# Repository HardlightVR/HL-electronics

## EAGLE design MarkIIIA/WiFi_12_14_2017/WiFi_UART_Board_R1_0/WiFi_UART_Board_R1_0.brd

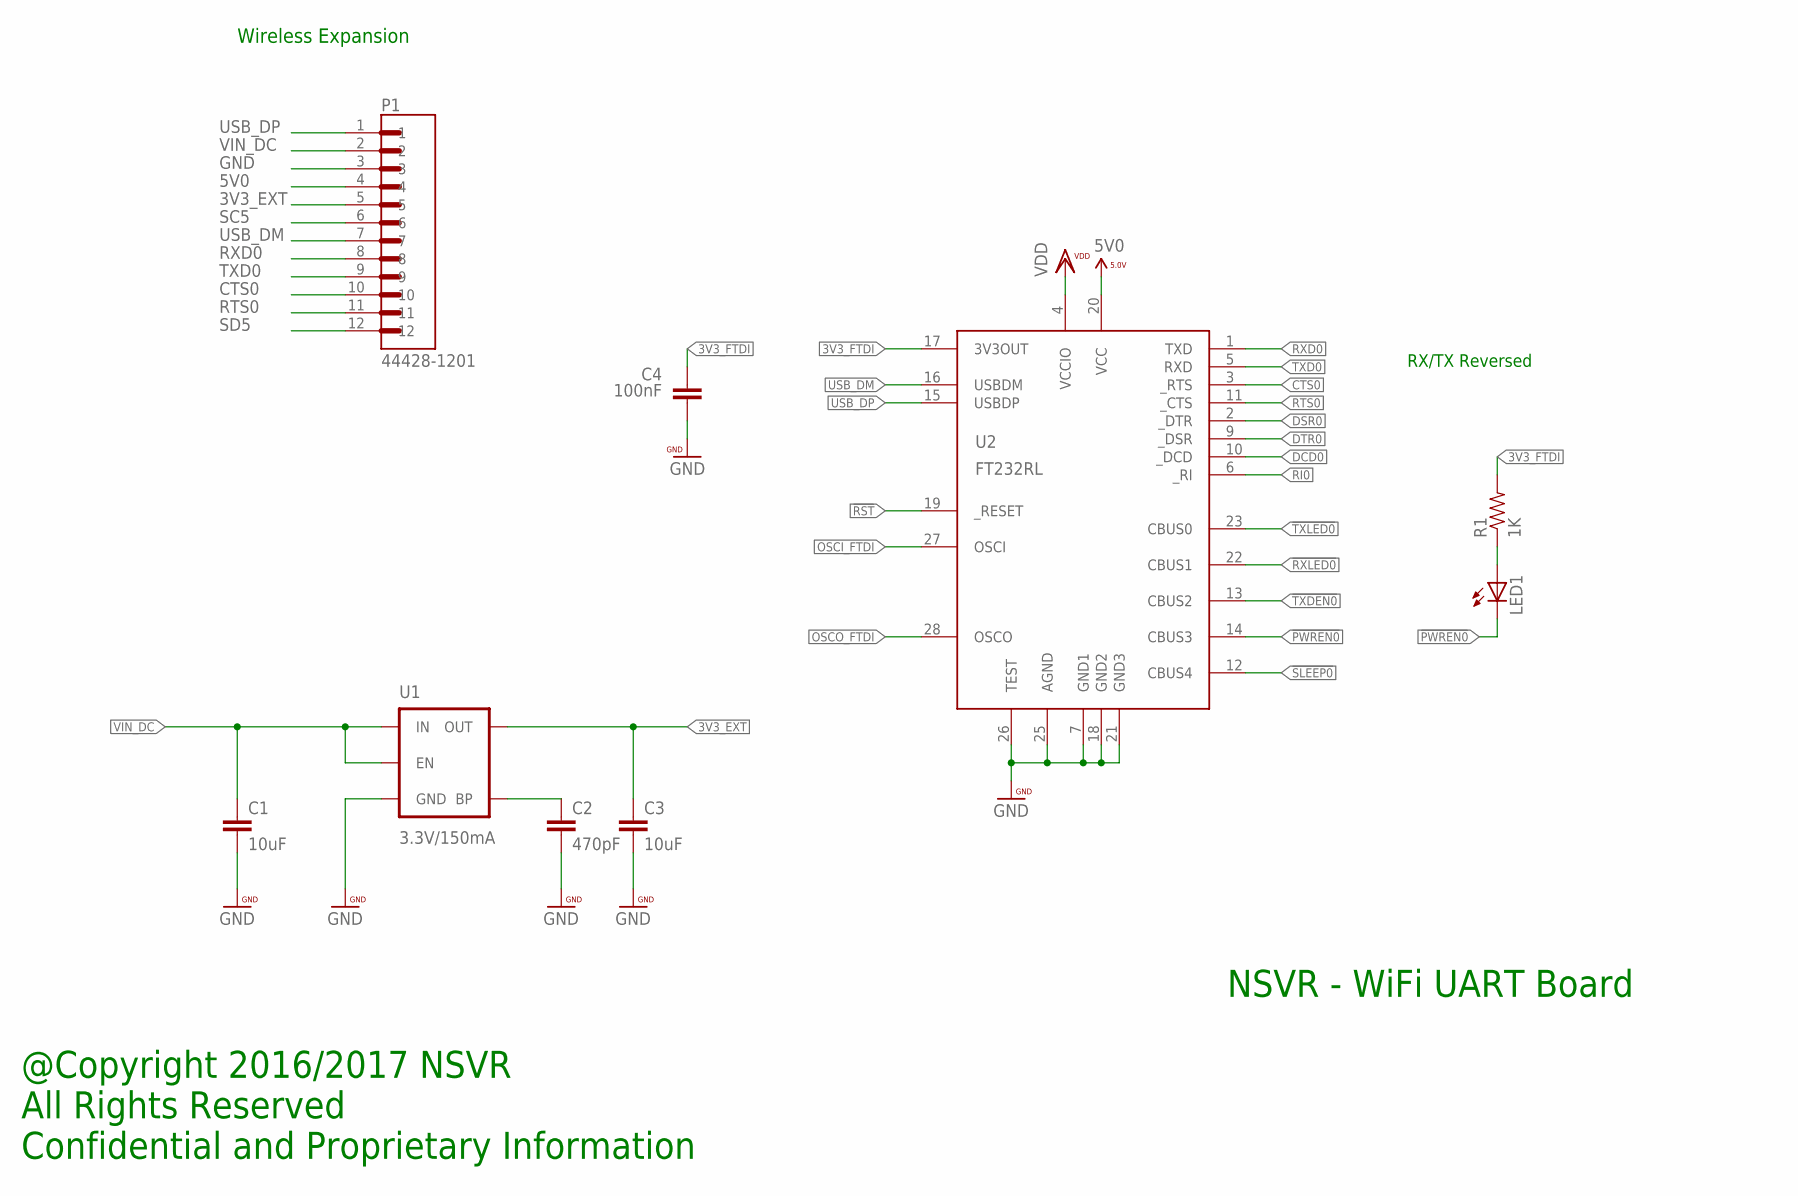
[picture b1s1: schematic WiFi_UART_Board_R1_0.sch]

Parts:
C1, C3: 10uF; 0603-CAP
C2: 470pF; 0402-CAP
C4: 100nF; 0402-CAP
LED1: LEDCHIP-LED0603; CHIP-LED0603
P1: 44428-1201; MOLEX_44428-1201
R1: 1K; EIA-0402
U1: 3.3V/150mA; SOT23-5
U2: FT232RL; SSOP28DB

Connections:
3V3_EXT: C3.1, P1.5, U1.5 (OUT)
3V3_FTDI: C4.1, R1.2, U2.17 (3V3OUT)
5V0: P1.4, U2.20 (VCC)
!PWREN0: LED1.C, U2.14 (CBUS3)
!RST: U2.19 (_RESET)
!RXLED0: U2.22 (CBUS1)
!SLEEP0: U2.12 (CBUS4)
!TXDEN0: U2.13 (CBUS2)
!TXLED0: U2.23 (CBUS0)
CTS0: P1.10, U2.3 (_RTS)
DCD0: U2.10 (_DCD)
DSR0: U2.2 (_DTR)
DTR0: U2.9 (_DSR)
GND: C1.2, C2.2, C3.2, C4.2, P1.3, U1.2 (GND), U2.7 (GND1), U2.18 (GND2), U2.21 (GND3), U2.25 (AGND), U2.26 (TEST)
unnamed: LED1.A, R1.1
unnamed: C2.1, U1.4 (BP)
OSCI_FTDI: U2.27 (OSCI)
OSCO_FTDI: U2.28 (OSCO)
RI0: U2.6 (_RI)
RTS0: P1.11, U2.11 (_CTS)
RXD0: P1.8, U2.1 (TXD)
SC5: P1.6
SD5: P1.12
TXD0: P1.9, U2.5 (RXD)
USB_DM: P1.7, U2.16 (USBDM)
USB_DP: P1.1, U2.15 (USBDP)
VDD: U2.4 (VCCIO)
VIN_DC: C1.1, P1.2, U1.1 (IN), U1.3 (EN)

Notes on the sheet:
@Copyright 2016/2017 NSVR All Rights Reserved Confidential and Proprietary Information
NSVR - WiFi UART Board
Wireless Expansion
RX/TX Reversed

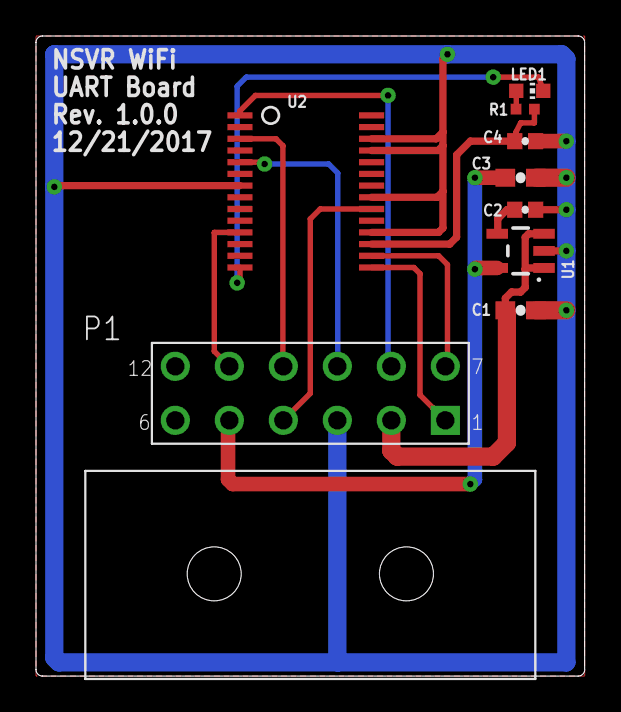
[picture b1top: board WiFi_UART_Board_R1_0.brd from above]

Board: 2 copper layers, 30.5 x 35.6 mm, 9 parts (0 on the bottom side), 14 nets.

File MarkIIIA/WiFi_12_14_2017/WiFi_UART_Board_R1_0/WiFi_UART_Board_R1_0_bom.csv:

"Qty";"Value";"Device";"Package";"Parts";"Description";"";
"1";"";"LEDCHIP-LED0603";"CHIP-LED0603";"LED1";"LED";"";
"1";"100nF";"CAP0402-CAP";"0402-CAP";"C4";"Capacitor";"";
"2";"10uF";"CAP0603-CAP";"0603-CAP";"C1, C3";"Capacitor";"";
"1";"1K";"RESISTOR0402-TYP";"EIA-0402";"R1";"Resistor";"";
"1";"3.3V/150mA";"V_REG_MIC52053.3V";"SOT23-5";"U1";"V_REG MIC5205 Standard 3.3V, 5V, and Adjustable 150mA LDO voltage regulator in SOT-23 layout. Micrel part MIC5205. BP (by-pass) pin is used to lower output noise with 470pF cap, may be left open. On the adjustable version BP is used to set output.";"";
"1";"44428-1201";"44428-1201";"MOLEX_44428-1201";"P1";"Conn Wire to Board HDR 12 POS 3mm Solder RA Thru-Hole Micro-Fit 3.0 BMI? Tray";"";
"1";"470pF";"CAP0402-CAP";"0402-CAP";"C2";"Capacitor";"";
"1";"FT232RL";"FT232RL";"SSOP28DB";"U2";"USB UART";"";

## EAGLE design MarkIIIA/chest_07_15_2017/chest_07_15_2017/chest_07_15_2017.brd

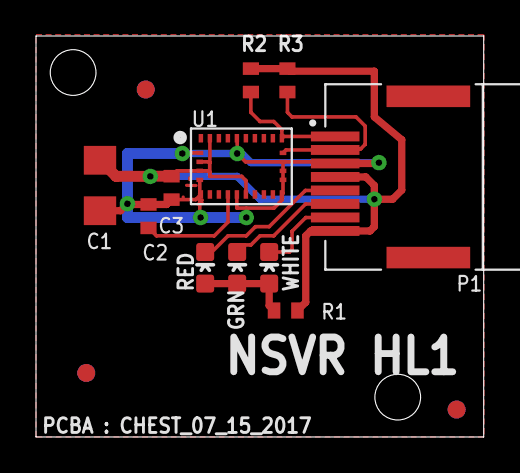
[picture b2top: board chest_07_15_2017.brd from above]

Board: 2 copper layers, 24.9 x 22.3 mm, 15 parts (1 on the bottom side), 9 nets.

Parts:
C1: 47uF; 1206
C2, C3: 0.1u; C0402
GRN: LED-0603
P1: 503148-0890; MOLEX_503148-0890
R1: 220 Ohm; R0402
R2, R3: 4K7; R0402
RED: LED-0603
U1: BNO055
U$1, U$3, U$4: CIRCLE-1MM-3R
U$2: NSVR_LOGO
WHITE: LED-0603

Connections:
3.6V: C1.1, C3.1, P1.4, P1.8, R1.2, R2.2, R3.2, U1.3, U1.4, U1.11, U1.28
BYPASS: C2.1, U1.9
GND: C1.2, C2.2, C3.2, P1.3, U1.2, U1.5, U1.6, U1.10, U1.15, U1.16, U1.17, U1.18, U1.25
unnamed: GRN.A, R1.1, RED.A, WHITE.A
PWM_B: P1.7, WHITE.C
PWM_G: GRN.C, P1.6
PWM_R: P1.5, RED.C
SCL: P1.2, R3.1, U1.19
SDA: P1.1, R2.1, U1.20

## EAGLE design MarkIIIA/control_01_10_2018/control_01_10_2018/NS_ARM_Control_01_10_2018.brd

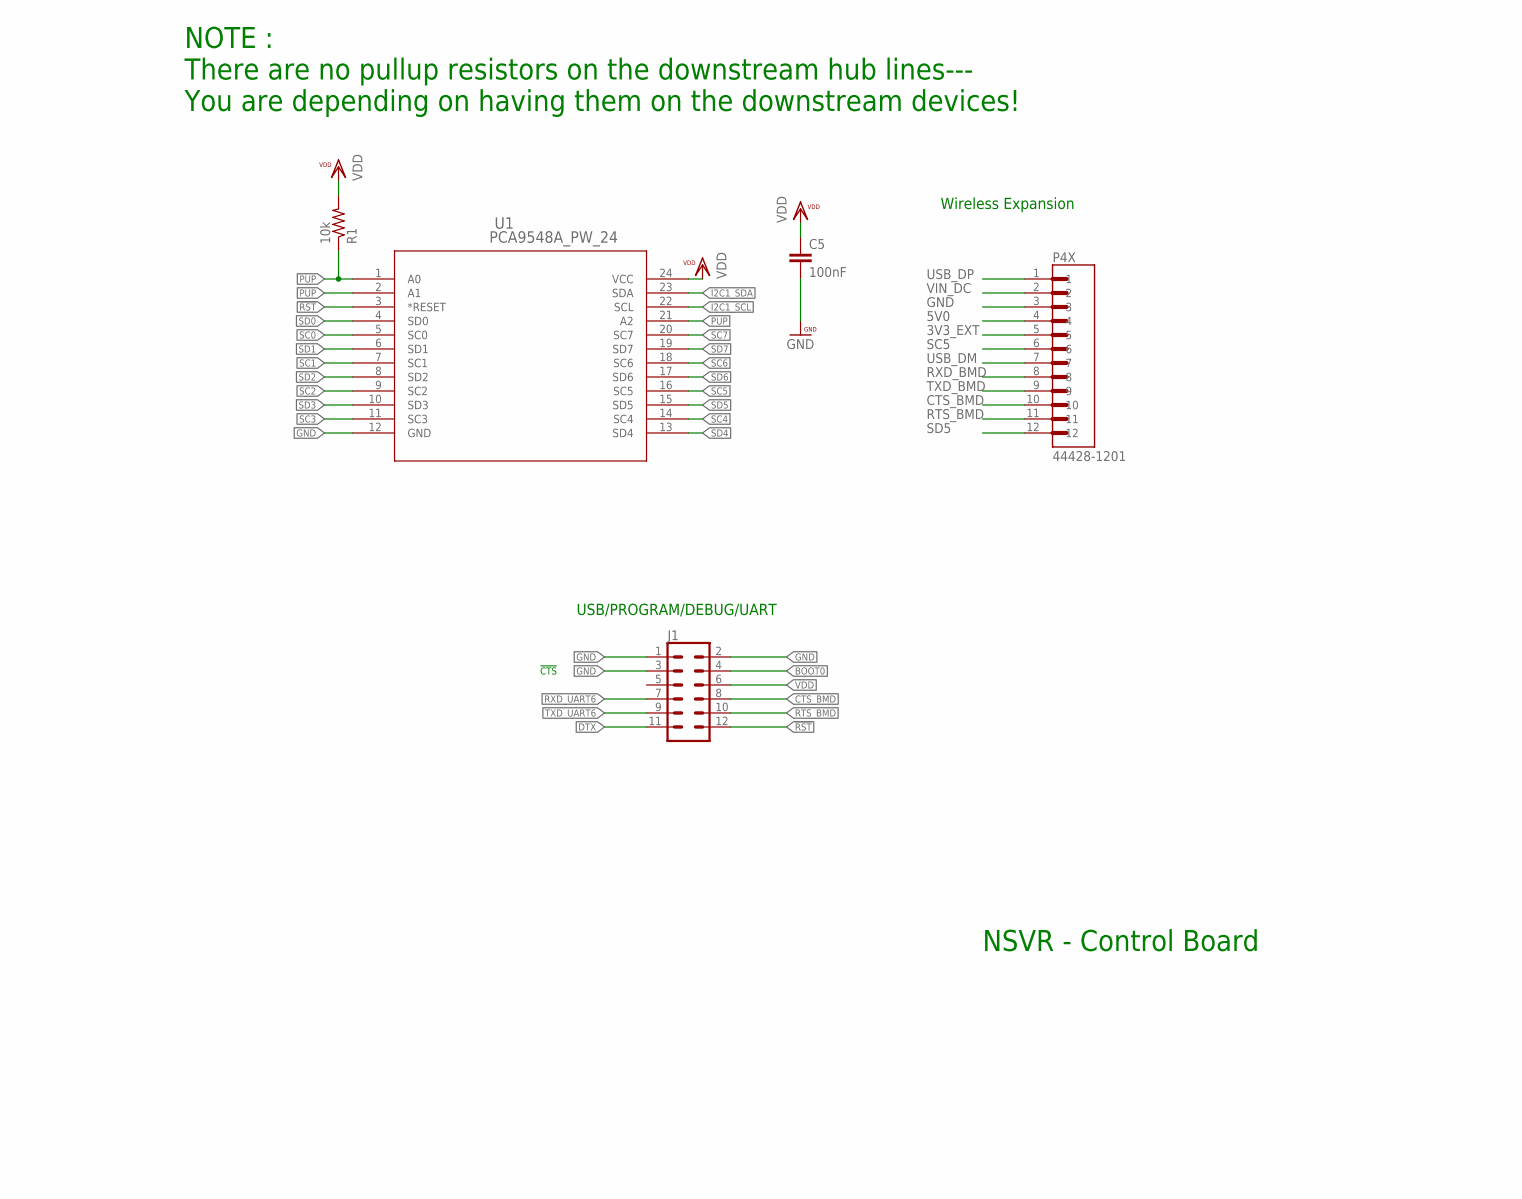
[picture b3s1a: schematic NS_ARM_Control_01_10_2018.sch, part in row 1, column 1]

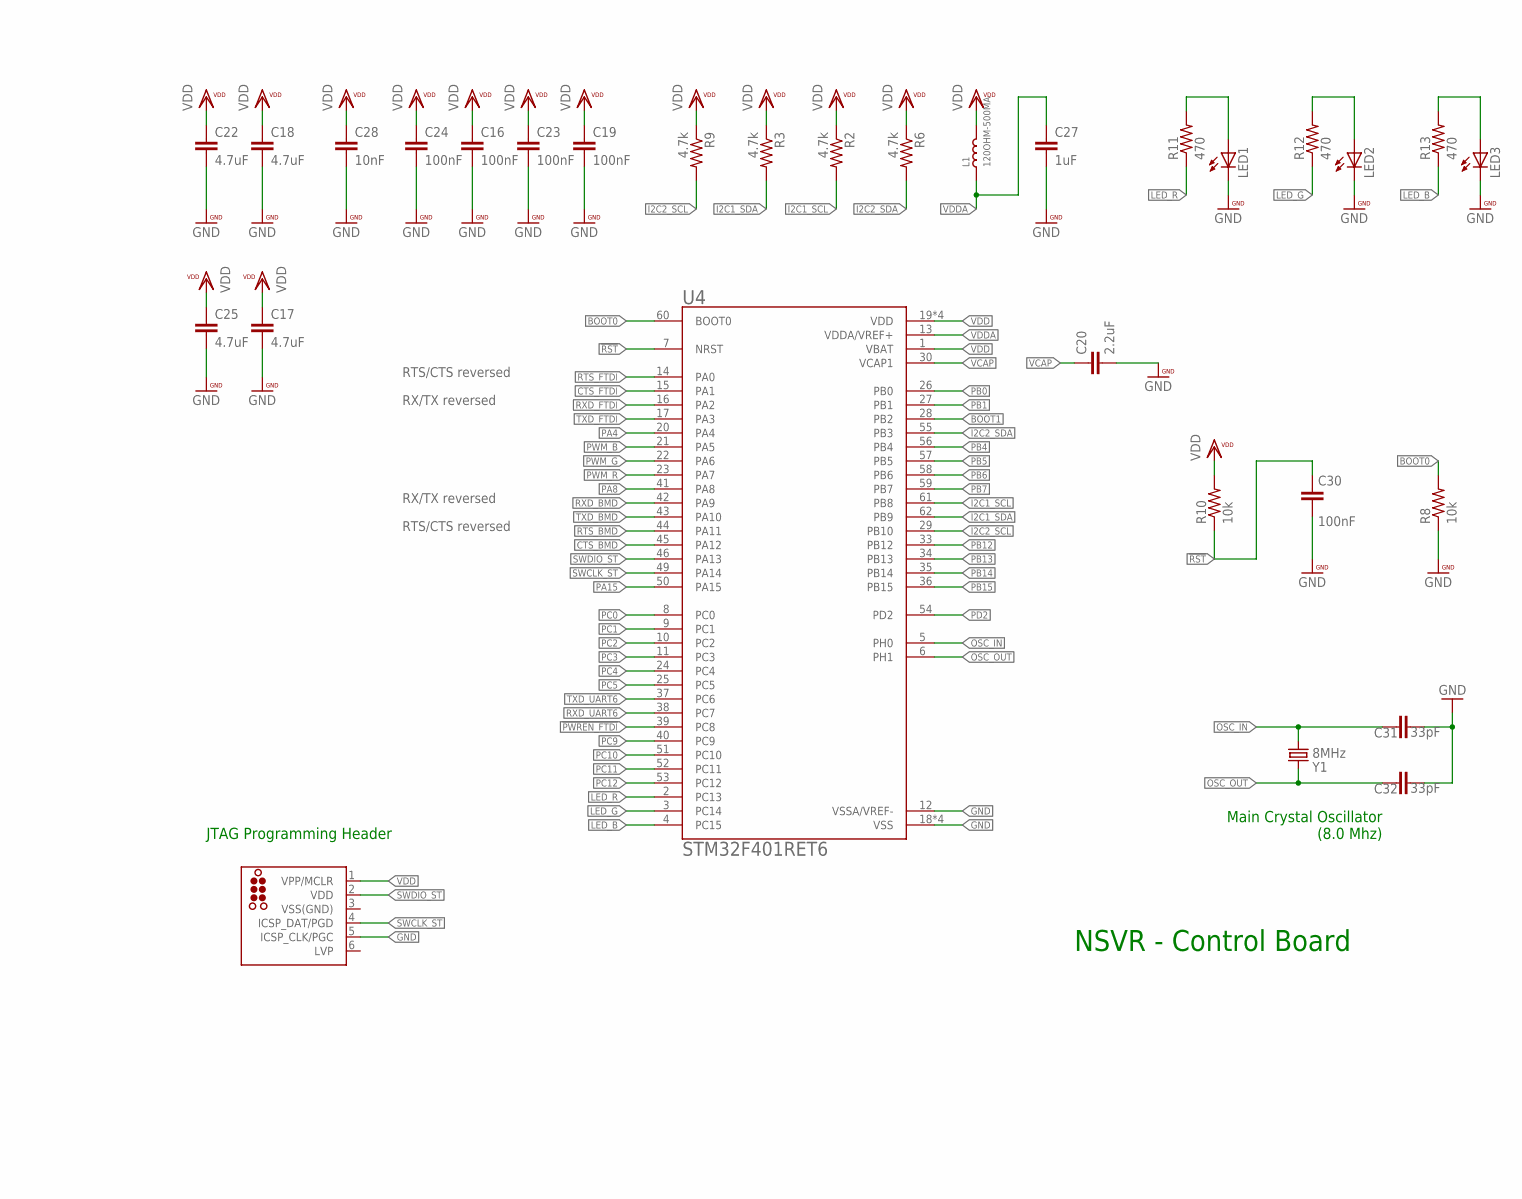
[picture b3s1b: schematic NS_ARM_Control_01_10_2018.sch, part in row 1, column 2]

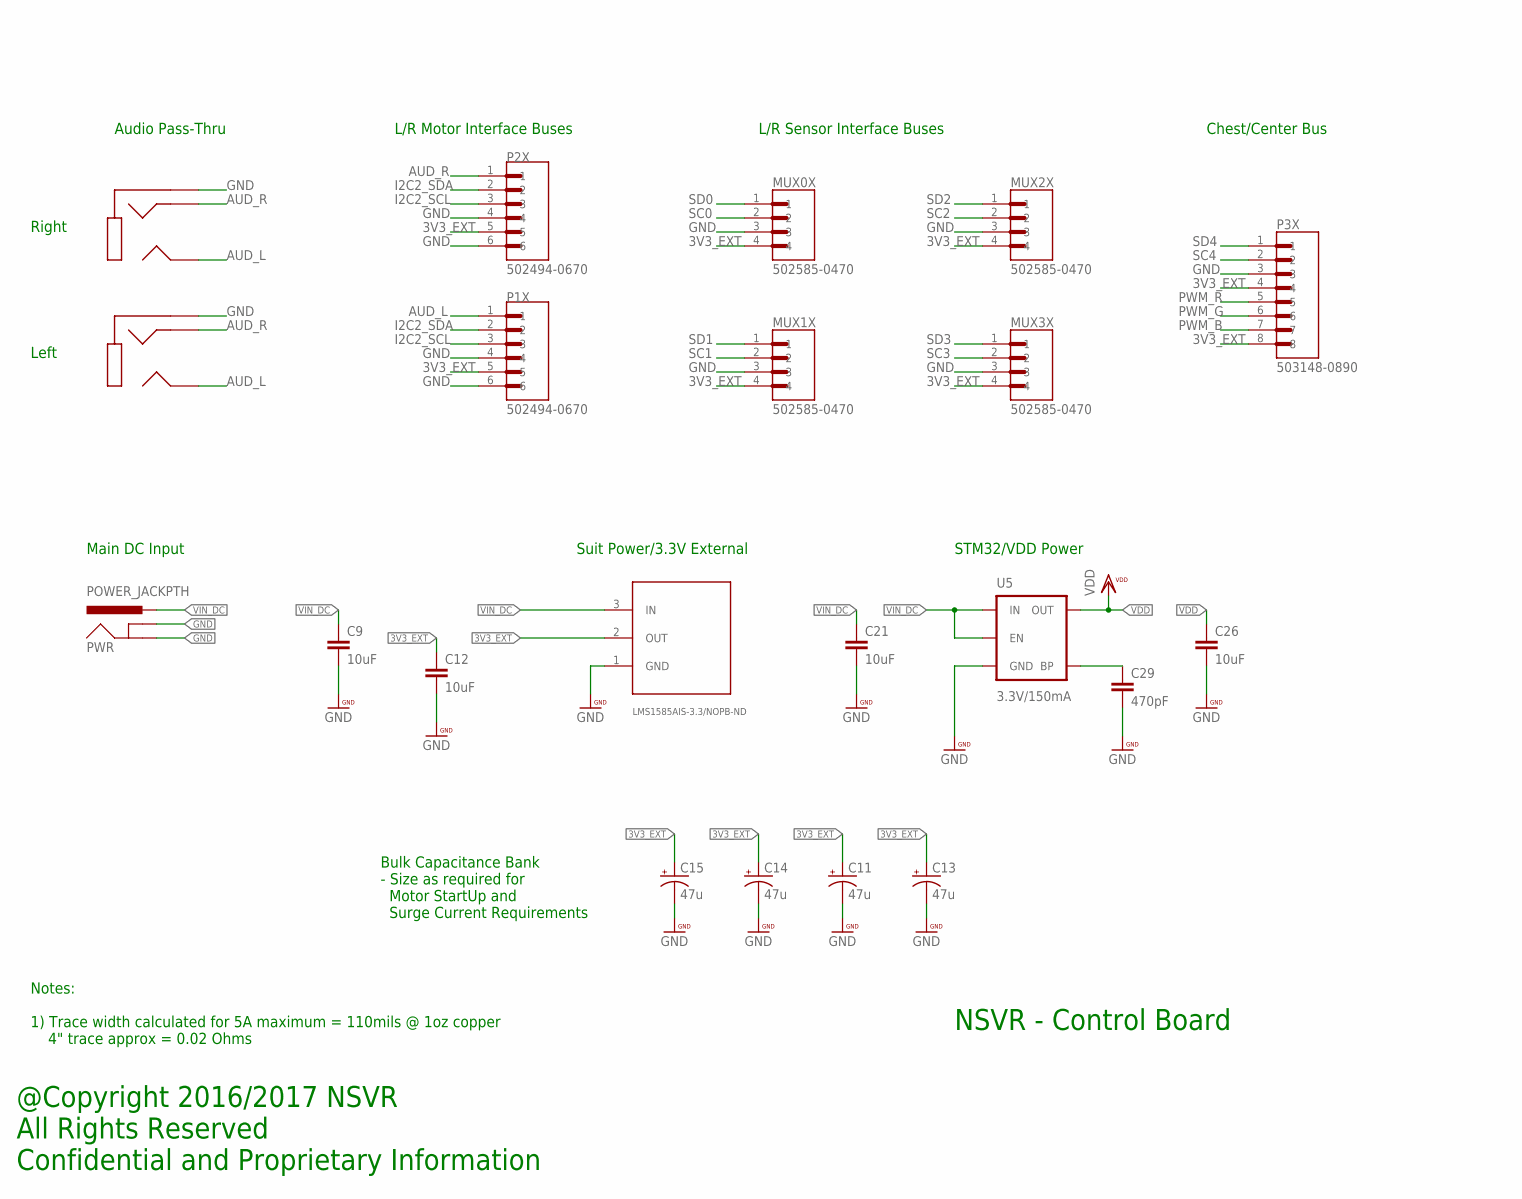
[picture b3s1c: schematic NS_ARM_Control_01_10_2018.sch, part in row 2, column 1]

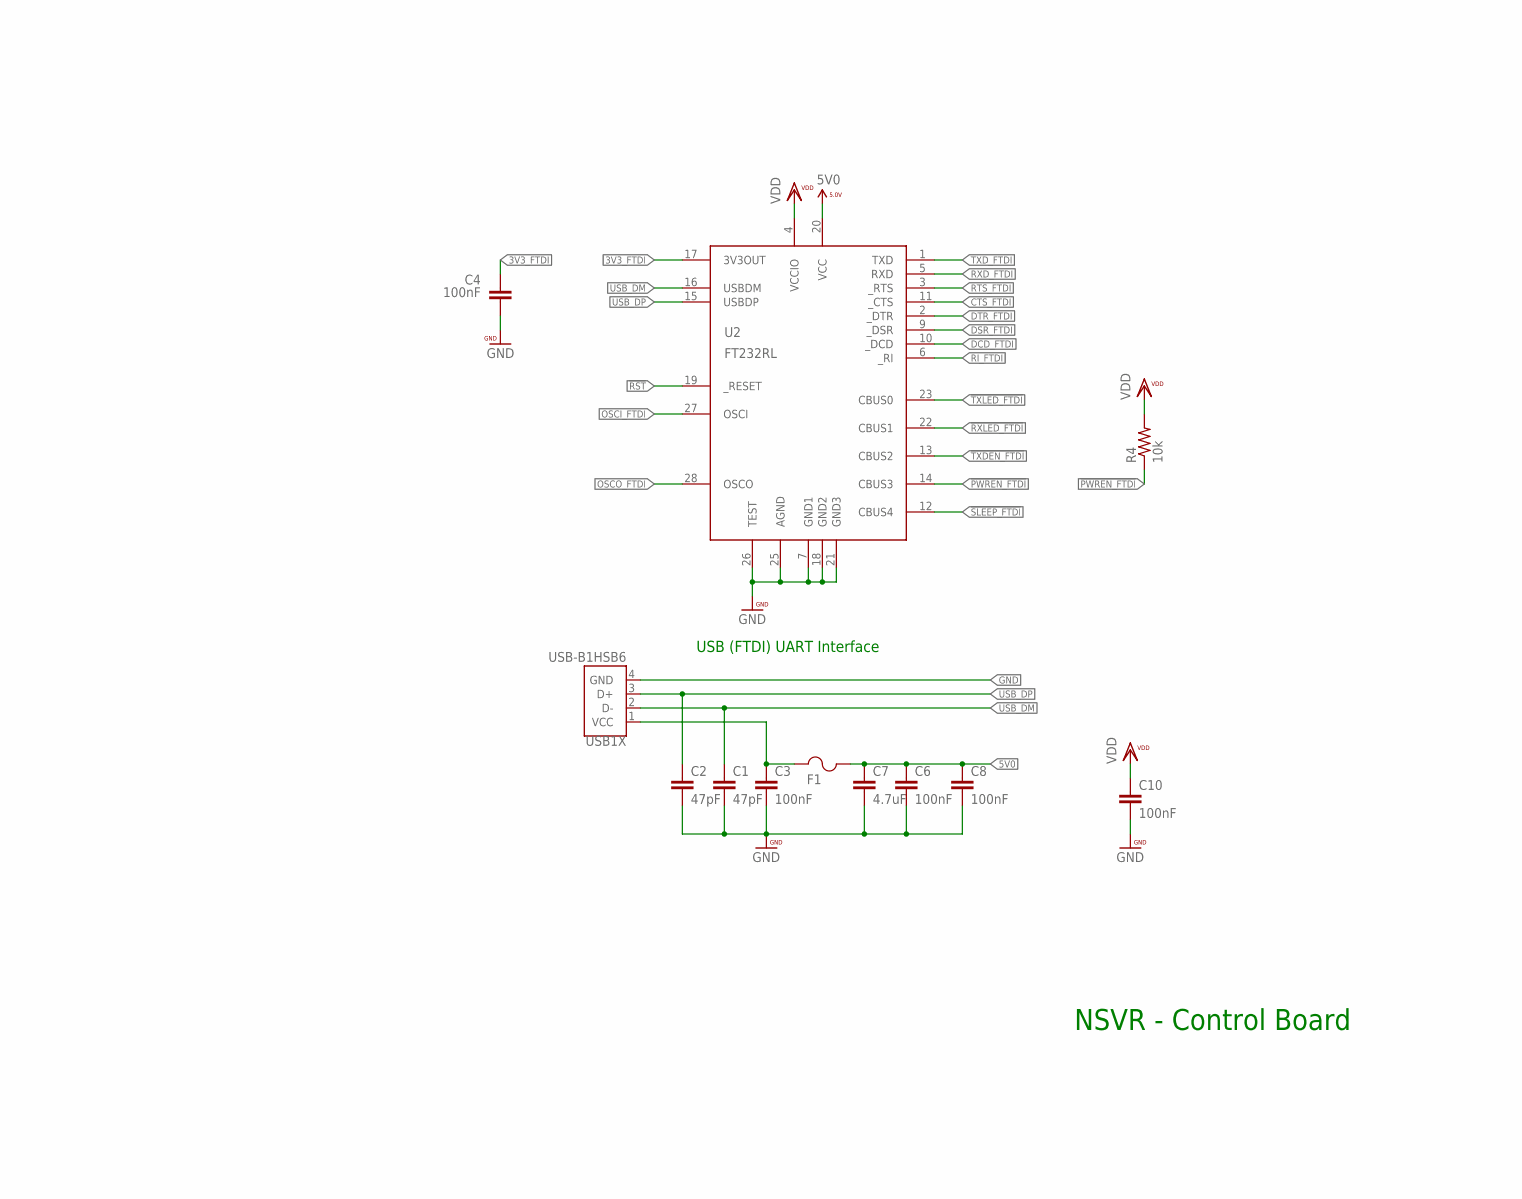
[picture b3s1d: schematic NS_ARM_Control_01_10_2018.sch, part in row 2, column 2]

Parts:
C1, C2: 47pF; 0402-CAP
C3, C4, C5, C6, C8, C10, C16, C19, C23, C24, C30: 100nF; 0402-CAP
C7, C17, C18, C22, C25: 4.7uF; 0402-CAP
C9, C12, C21, C26: 10uF; 0603-CAP
C11, C13, C14, C15: 47u; PANASONIC_D
C20: 2.2uF; 0402-CAP
C27: 1uF; 0402-CAP
C28: 10nF; 0402-CAP
C29: 470pF; 0402-CAP
C31, C32: 33pF; 0402-CAP
F1: 1206L050YR; 1206LSERIES
J1: CONN_06X2SMD_FEMALE; 2X6_SMD
J_ST: TC2030-MCP-NL
L1: 120OHM-500MA; L0603
LED1, LED2, LED3: LEDCHIP-LED0603; CHIP-LED0603
MUX0X, MUX1X, MUX2X, MUX3X: 502585-0470; MOLEX_502585-0470
P1X, P2X: 502494-0670; MOLEX_502494-0670
P3X: 503148-0890; MOLEX_503148-0890
P4X: 44428-1201; MOLEX_44428-1201
PJ1, PJ2: SJ1-3513N; SJ1-351XN
PWR: POWER_JACKPTH; POWER_JACK_PTH
R1, R4, R8, R10: 10k; EIA-0402
R2, R3, R6, R9: 4.7k; EIA-0402
R11, R12, R13: 470; EIA-0402
U1: PCA9548A_PW_24; PW24
U2: FT232RL; SSOP28DB
U3: LMS1585AIS-3.3/NOPB-ND; TO254P1524X483-4N
U4: STM32F401RET6; QFP50P1200X1200X160-64N
U5: 3.3V/150mA; SOT23-5
USB1X: USB-B1HSB6; OST_USB-B1HSB6
Y1: 8MHz; CRYSTAL-SMD-5X3

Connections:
3V3_EXT: C11.+, C12.1, C13.+, C14.+, C15.+, MUX0X.4, MUX1X.4, MUX2X.4, MUX3X.4, P1X.5, P2X.5, P3X.4, P3X.8, P4X.5, U3.2 (OUT)
3V3_FTDI: C4.1, U2.17 (3V3OUT)
5V0: C6.1, C7.1, C8.1, F1.2, P4X.4, U2.20 (VCC)
!PWREN_FTDI: R4.1, U2.14 (CBUS3), U4.39 (PC8)
!RST: C30.1, J1.12, R10.1, U1.3 (*RESET), U2.19 (_RESET), U4.7 (NRST)
!RXLED_FTDI: U2.22 (CBUS1)
!SLEEP_FTDI: U2.12 (CBUS4)
!TXDEN_FTDI: U2.13 (CBUS2)
!TXLED_FTDI: U2.23 (CBUS0)
AUD_L: P1X.1, PJ1.2, PJ2.2
AUD_R: P2X.1, PJ1.3, PJ2.3
BOOT0: J1.4, R8.2, U4.60 (BOOT0)
BOOT1: U4.28 (PB2)
CTS_BMD: J1.8, P4X.10, U4.45 (PA12)
CTS_FTDI: U2.11 (_CTS), U4.15 (PA1)
DCD_FTDI: U2.10 (_DCD)
DSR_FTDI: U2.9 (_DSR)
DTR_FTDI: U2.2 (_DTR)
DTX: J1.11
GND: C1.2, C2.2, C3.2, C4.2, C5.2, C6.2, C7.2, C8.2, C9.2, C10.2, C11.-, C12.2, C13.-, C14.-, C15.-, C16.2, C17.2, C18.2, C19.2, C20.2, C21.2, C22.2, C23.2, C24.2, C25.2, C26.2, C27.2, C28.2, C29.2, C30.2, C31.1, C32.1, J1.1, J1.2, J1.3, J_ST.5 (ICSP_CLK/PGC), LED1.C, LED2.C, LED3.C, MUX0X.3, MUX1X.3, MUX2X.3, MUX3X.3, P1X.4, P1X.6, P2X.4, P2X.6, P3X.3, P4X.3, PJ1.1, PJ2.1, PWR.GND, PWR.GNDBREAK, R8.1, U1.12 (GND), U2.7 (GND1), U2.18 (GND2), U2.21 (GND3), U2.25 (AGND), U2.26 (TEST), U3.1 (GND), U4.12 (VSSA/VREF-), U4.18 (VSS), U4.31 (VSS), U4.47 (VSS), U4.63 (VSS), U5.2 (GND), USB1X.4 (GND)
I2C1_SCL: R2.2, U1.22 (SCL), U4.61 (PB8)
I2C1_SDA: R3.2, U1.23 (SDA), U4.62 (PB9)
I2C2_SCL: P1X.3, P2X.3, R9.2, U4.29 (PB10)
I2C2_SDA: P1X.2, P2X.2, R6.2, U4.55 (PB3)
LED1: LED1.A, R11.2
LED2: LED2.A, R12.2
LED3: LED3.A, R13.2
LED_B: R13.1, U4.4 (PC15)
LED_G: R12.1, U4.3 (PC14)
LED_R: R11.1, U4.2 (PC13)
unnamed: C29.1, U5.4 (BP)
OSCI_FTDI: U2.27 (OSCI)
OSCO_FTDI: U2.28 (OSCO)
OSC_IN: C31.2, U4.5 (PH0), Y1.1
OSC_OUT: C32.2, U4.6 (PH1), Y1.3 (2)
PA4: U4.20 (PA4)
PA8: U4.41 (PA8)
PA15: U4.50 (PA15)
PB0: U4.26 (PB0)
PB1: U4.27 (PB1)
PB4: U4.56 (PB4)
PB5: U4.57 (PB5)
PB6: U4.58 (PB6)
PB7: U4.59 (PB7)
PB12: U4.33 (PB12)
PB13: U4.34 (PB13)
PB14: U4.35 (PB14)
PB15: U4.36 (PB15)
PC0: U4.8 (PC0)
PC1: U4.9 (PC1)
PC2: U4.10 (PC2)
PC3: U4.11 (PC3)
PC4: U4.24 (PC4)
PC5: U4.25 (PC5)
PC9: U4.40 (PC9)
PC10: U4.51 (PC10)
PC11: U4.52 (PC11)
PC12: U4.53 (PC12)
PD2: U4.54 (PD2)
PUP: R1.1, U1.1 (A0), U1.2 (A1), U1.21 (A2)
PWM_B: P3X.7, U4.21 (PA5)
PWM_G: P3X.6, U4.22 (PA6)
PWM_R: P3X.5, U4.23 (PA7)
RI_FTDI: U2.6 (_RI)
RTS_BMD: J1.10, P4X.11, U4.44 (PA11)
RTS_FTDI: U2.3 (_RTS), U4.14 (PA0)
RXD_BMD: P4X.8, U4.42 (PA9)
RXD_FTDI: U2.5 (RXD), U4.16 (PA2)
RXD_UART6: J1.7, U4.38 (PC7)
SC0: MUX0X.2, U1.5 (SC0)
SC1: MUX1X.2, U1.7 (SC1)
SC2: MUX2X.2, U1.9 (SC2)
SC3: MUX3X.2, U1.11 (SC3)
SC4: P3X.2, U1.14 (SC4)
SC5: P4X.6, U1.16 (SC5)
SC6: U1.18 (SC6)
SC7: U1.20 (SC7)
SD0: MUX0X.1, U1.4 (SD0)
SD1: MUX1X.1, U1.6 (SD1)
SD2: MUX2X.1, U1.8 (SD2)
SD3: MUX3X.1, U1.10 (SD3)
SD4: P3X.1, U1.13 (SD4)
SD5: P4X.12, U1.15 (SD5)
SD6: U1.17 (SD6)
SD7: U1.19 (SD7)
SWCLK_ST: J_ST.4 (ICSP_DAT/PGD), U4.49 (PA14)
SWDIO_ST: J_ST.2 (VDD), U4.46 (PA13)
TXD_BMD: P4X.9, U4.43 (PA10)
TXD_FTDI: U2.1 (TXD), U4.17 (PA3)
TXD_UART6: J1.9, U4.37 (PC6)
USB_DM: C1.1, P4X.7, U2.16 (USBDM), USB1X.2 (D-)
USB_DP: C2.1, P4X.1, U2.15 (USBDP), USB1X.3 (D+)
VBUS_IN: C3.1, F1.1, USB1X.1 (VCC)
VCAP: C20.1, U4.30 (VCAP1)
VDD: C5.1, C10.1, C16.1, C17.1, C18.1, C19.1, C22.1, C23.1, C24.1, C25.1, C26.1, C28.1, J1.6, J_ST.1 (VPP/MCLR), L1.2, R1.2, R2.1, R3.1, R4.2, R6.1, R9.1, R10.2, U1.24 (VCC), U2.4 (VCCIO), U4.1 (VBAT), U4.19 (VDD), U4.32 (VDD), U4.48 (VDD), U4.64 (VDD), U5.5 (OUT)
VDDA: C27.1, L1.1, U4.13 (VDDA/VREF+)
VIN_DC: C9.1, C21.1, P4X.2, PWR.PWR, U3.3 (IN), U5.1 (IN), U5.3 (EN)
VSS(GND): J_ST.3 (VSS(GND))

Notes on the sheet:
RX/TX reversed
RTS/CTS reversed
NSVR - Control Board
@Copyright 2016/2017 NSVR All Rights Reserved Confidential and Proprietary Information
Main Crystal Oscillator (8.0 Mhz)
JTAG Programming Header
USB (FTDI) UART Interface
STM32/VDD Power
Audio Pass-Thru
Wireless Expansion
L/R Motor Interface Buses
Right
Left
Chest/Center Bus
L/R Sensor Interface Buses
Bulk Capacitance Bank - Size as required for Motor StartUp and Surge Current Requirements
Notes: 1) Trace width calculated for 5A maximum = 110mils @ 1oz copper 4" trace approx = 0.02 Ohms
Suit Power/3.3V External
Main DC Input
NOTE : There are no pullup resistors on the downstream hub lines--- You are depending on having them on the downstream devices!
USB/PROGRAM/DEBUG/UART
!CTS

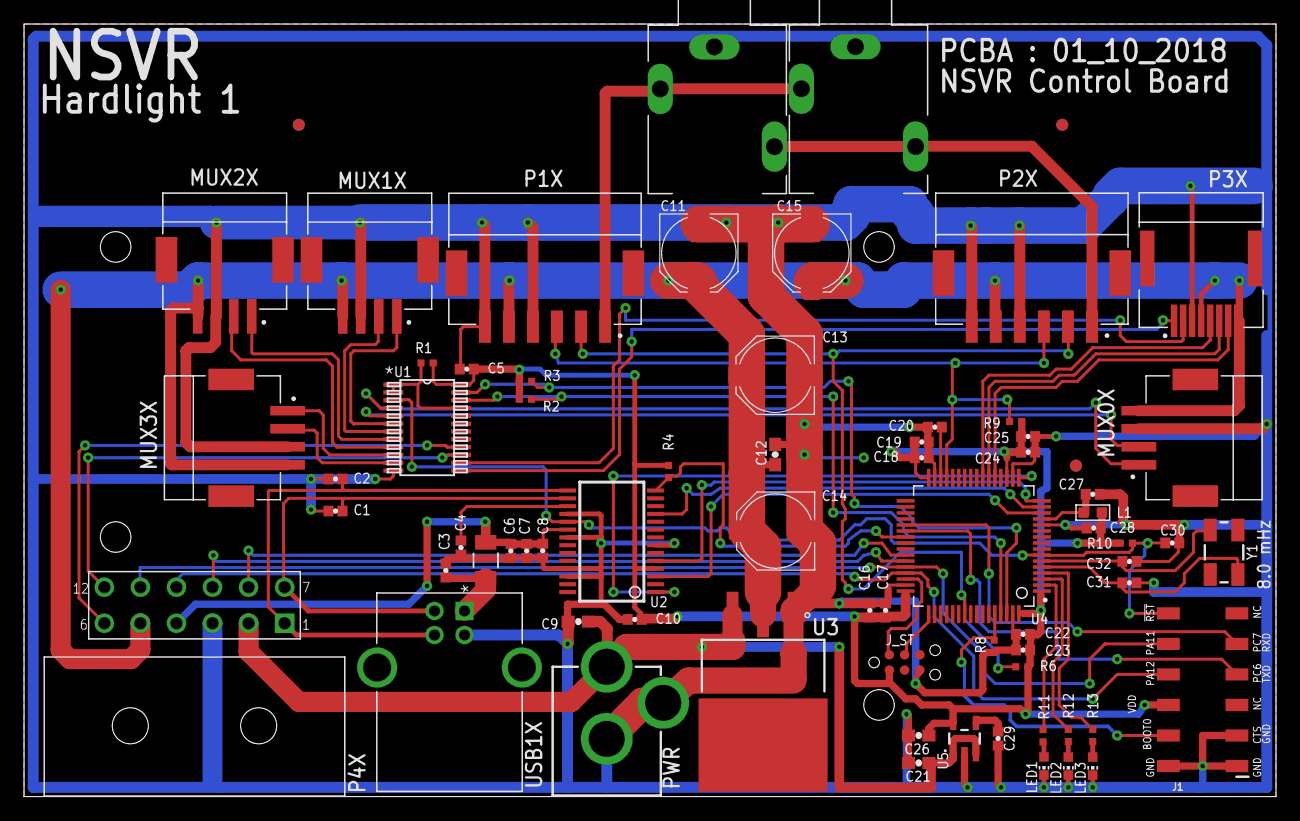
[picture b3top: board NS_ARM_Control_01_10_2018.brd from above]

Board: 2 copper layers, 104.1 x 64.3 mm, 72 parts (1 on the bottom side), 57 nets.

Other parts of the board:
U$1, U$2, U$3: CIRCLE-1MM-3R
U$100: NSVR_LOGO

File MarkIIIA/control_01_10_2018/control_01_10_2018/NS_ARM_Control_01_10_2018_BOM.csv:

Qty,Value,Device,Package,Parts,Description
1,,95278-801A12LF,2X6_SMD,J1,95278-801A12LF
3,,LEDCHIP-LED0603,CHIP-LED0603,"LED1, LED2, LED3",LED
1,,TC2030-MCP-NL,TC2030-MCP-NL,J_ST,TAG-CONNECT ICSP ConnectorManufacturer: Tag-Connect
11,100nF,CAP0402-CAP,0402-CAP,"C3, C4, C5, C6, C8, C10, C16, C19, C23, C24, C30",Capacitor
4,10k,RESISTOR0402-TYP,EIA-0402,"R1, R4, R8, R10",Resistor
1,10nF,CAP0402-CAP,0402-CAP,C28,Capacitor
4,10uF,CAP0603-CAP,0603-CAP,"C9, C12, C21, C26",Capacitor
1,1206L050YR,1206L050YR,1206LSERIES,F1,
1,120OHM-500MA,SMD-FERRITE-CHIP-120-OHM-500MA(0603),L0603,L1,303030001
1,1uF,CAP0402-CAP,0402-CAP,C27,Capacitor
1,2.2uF,CAP0402-CAP,0402-CAP,C20,Capacitor
1,3.3V/150mA,V_REG_MIC52053.3V,SOT23-5,U5,"V_REG MIC5205 Standard 3.3V, 5V, and Adjustable 150mA LDO voltage regulator in SOT-23 layout. Micrel part MIC5205. BP (by-pass) pin is used to lower output noise with 470pF cap, may be left open. On the adjustable version BP is used to set output."
2,33pF,CAP0402-CAP,0402-CAP,"C31, C32",Capacitor
4,4.7k,RESISTOR0402-TYP,EIA-0402,"R2, R3, R6, R9",Resistor
5,4.7uF,CAP0402-CAP,0402-CAP,"C7, C17, C18, C22, C25",Capacitor
1,44428-1201,44428-1201,MOLEX_44428-1201,P4X,Conn Wire to Board HDR 12 POS 3mm Solder RA Thru-Hole Micro-Fit 3.0 BMI? Tray
3,470,RESISTOR0402-TYP,EIA-0402,"R11, R12, R13",Resistor
1,470pF,CAP0402-CAP,0402-CAP,C29,Capacitor
2,47pF,CAP0402-CAP,0402-CAP,"C1, C2",Capacitor
4,47u,CAP_POLD,PANASONIC_D,"C11, C13, C14, C15",Capacitor Polarized
2,502494-0670,502494-0670,MOLEX_502494-0670,"P1X, P2X","2.00mm Pitch CLIK-Mate Wire-to-Board PCB Receptacle, Single Row, Right Angle, 6 Circuits"
4,502585-0470,502585-0470,MOLEX_502585-0470,"MUX0X, MUX1X, MUX2X, MUX3X","1.50mm Pitch CLIK-Mate Wire-to-Board PCB Receptacle, Single Row, Right Angle, 4 Circuits"
1,503148-0890,503148-0890,MOLEX_503148-0890,P3X,1.5wb Dual r/a Embs Tape Pkg 8p
1,8MHz,CRYSTAL5X3,CRYSTAL-SMD-5X3,Y1,Crystals
1,FT232RL,FT232RL,SSOP28DB,U2,USB UART
1,LMS1585AIS-3.3/NOPB-ND,LMS1585AIS-3.3/NOPB-ND,TO254P1524X483-4N,U3,
1,PCA9548A_PW_24,PCA9548A_PW_24,PW24,U1,
1,POWER_JACKPTH,POWER_JACKPTH,POWER_JACK_PTH,PWR,Power Jack
2,SJ1-3513N,SJ1-3513N,SJ1-351XN,"PJ1, PJ2",
1,STM32F401RET6,STM32F401RET6,QFP50P1200X1200X160-64N,U4,MCU 32-Bit STM32 ARM Cortex M4 RISC 512KB Flash 1.8V/2.5V/3.3V 64-Pin LQFP Tray
1,USB-B1HSB6,USB-B1HSB6,OST_USB-B1HSB6,USB1X,Conn Usb Type b r/a Black

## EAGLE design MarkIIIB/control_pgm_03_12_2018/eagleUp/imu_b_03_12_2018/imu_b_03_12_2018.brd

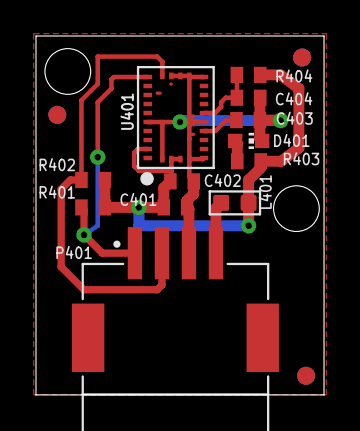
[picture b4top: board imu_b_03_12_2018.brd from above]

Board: 2 copper layers, 16.0 x 19.9 mm, 15 parts (0 on the bottom side), 8 nets.

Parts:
$$U$2: CIRCLE-1MM-2R
C401: 10uF; C0402
C402, C403, C404: 0.1u; C0402
D401: CHIP-LED0603
L401: 120OHM-500MA; L0603
P401: 502585-0470; MOLEX_502585-0470
R401, R402, R404: 4.7k; R0402
R403: 220; R0402
U401: BNO055
U$1, U$3: CIRCLE-1MM-2R

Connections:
3V3_EXT: L401.2, P401.4
!RST: C404.1, R404.2, U401.11
CAP: C403.1, U401.9
GND: C401.2, C402.2, C403.2, C404.2, D401.C, P401.3, U401.2, U401.5, U401.6, U401.10, U401.15, U401.16, U401.17, U401.18, U401.25
unnamed: D401.A, R403.2
SCL: P401.2, R402.2, U401.19
SDA: P401.1, R401.2, U401.20
VDD: C401.1, C402.1, L401.1, R401.1, R402.1, R403.1, R404.1, U401.3, U401.4, U401.28

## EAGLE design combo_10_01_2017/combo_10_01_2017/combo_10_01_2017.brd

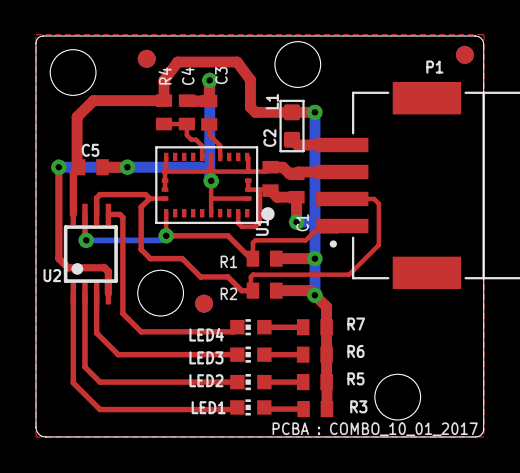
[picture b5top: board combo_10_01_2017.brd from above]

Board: 2 copper layers, 24.9 x 22.3 mm, 24 parts (1 on the bottom side), 15 nets.

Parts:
$$U$2: CIRCLE-1MM-2R
C1, C5: 10uF; C0402
C2, C3, C4: 0.1u; C0402
L1: 120OHM-500MA; L0603
LED1, LED2, LED3, LED4: CHIP-LED0603
P1: 502585-0470; MOLEX_502585-0470
R1, R2, R4: 4.7k; R0402
R3, R5, R6, R7: 100; R0402
U1: BNO055
U2: PCA9533DP; TSSOP8
U$1, U$3: CIRCLE-1MM-2R
U$5: NSVR_LOGO

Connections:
3V3_EXT: L1.2, P1.4
!RST: C4.1, R4.2, U1.11
CAP: C3.1, U1.9
GND: C1.2, C2.2, C3.2, C4.2, C5.2, P1.3, U1.2, U1.5, U1.6, U1.10, U1.15, U1.16, U1.17, U1.18, U1.25, U2.4
LED1: LED1.C, U2.1
LED2: LED2.C, U2.2
LED3: LED3.C, U2.3
LED4: LED4.C, U2.5
unnamed: LED1.A, R3.2
unnamed: LED2.A, R5.2
unnamed: LED3.A, R6.2
unnamed: LED4.A, R7.2
SCL: P1.2, R2.2, U1.19, U2.6
SDA: P1.1, R1.2, U1.20, U2.7
VDD: C1.1, C2.1, C5.1, L1.1, R1.1, R2.1, R3.1, R4.1, R5.1, R6.1, R7.1, U1.3, U1.4, U1.28, U2.8

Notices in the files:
parts and their libraries:
PatternAgents-ProtoPads: License : http://creativecommons.org/licenses/by-sa/4.0
(Creative Commons 4.0)
SparkFun-PowerIC: Licensing: Creative Commons ShareAlike 4.0 International - https://creativecommons.org/licenses/by-sa/4.0
COPYRIGHT: Copyright C 2015 Accelerated Designs. All rights reserved
